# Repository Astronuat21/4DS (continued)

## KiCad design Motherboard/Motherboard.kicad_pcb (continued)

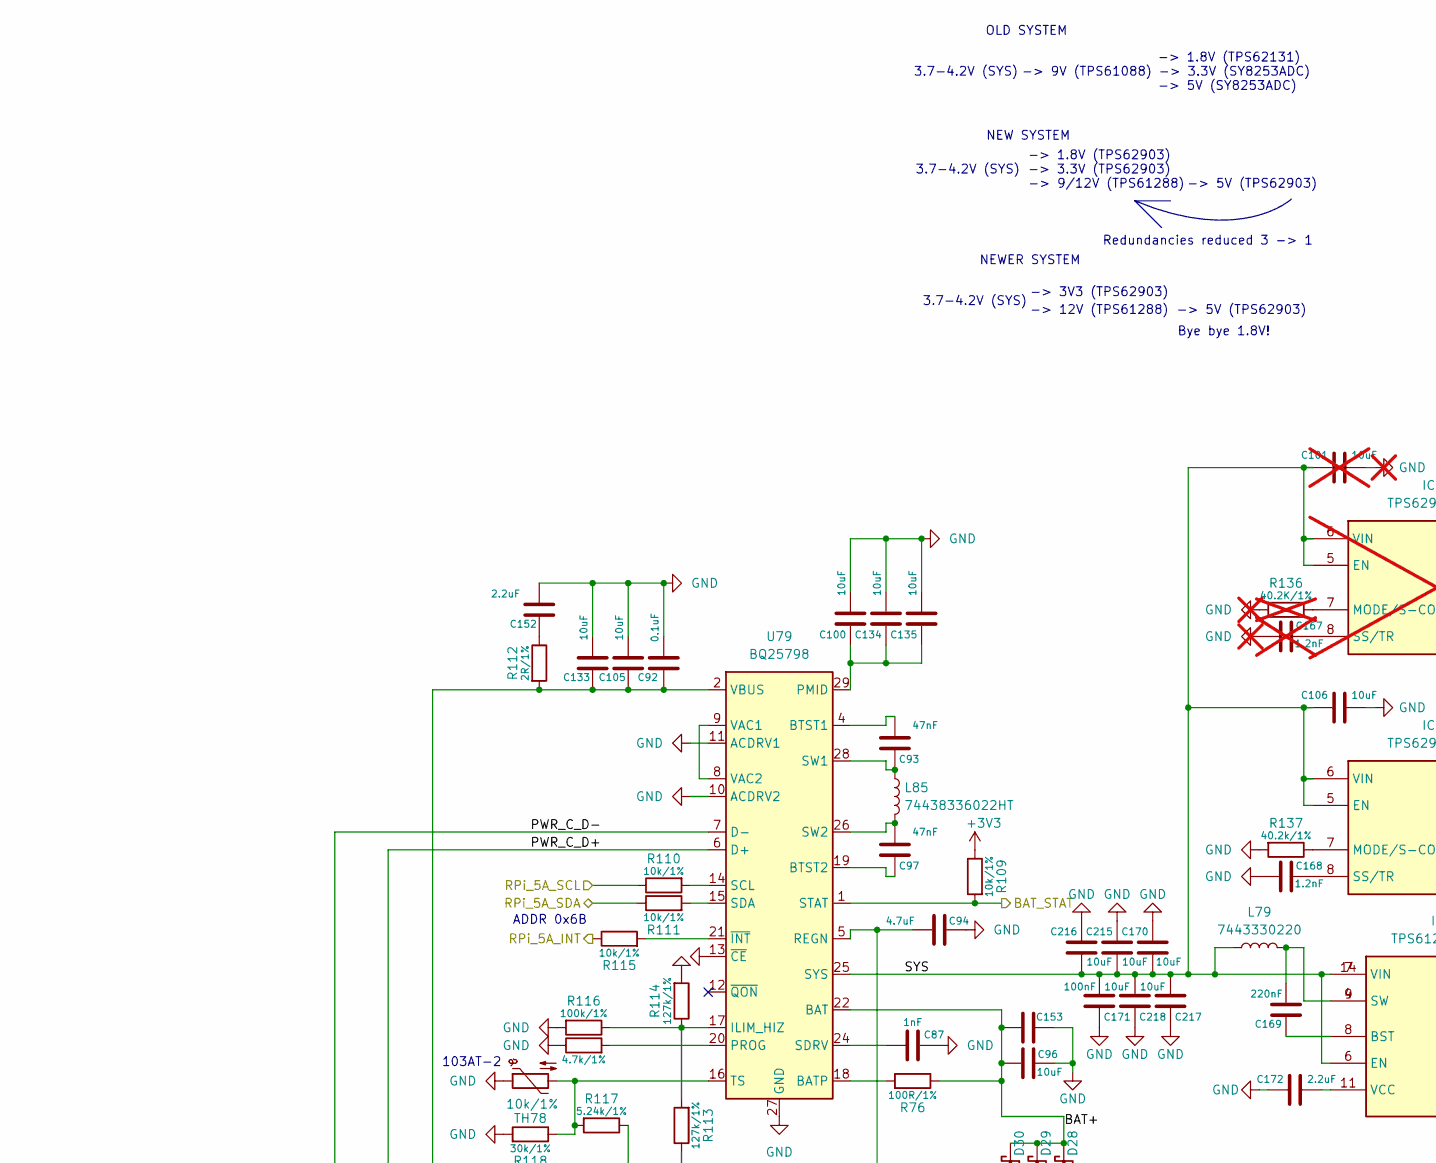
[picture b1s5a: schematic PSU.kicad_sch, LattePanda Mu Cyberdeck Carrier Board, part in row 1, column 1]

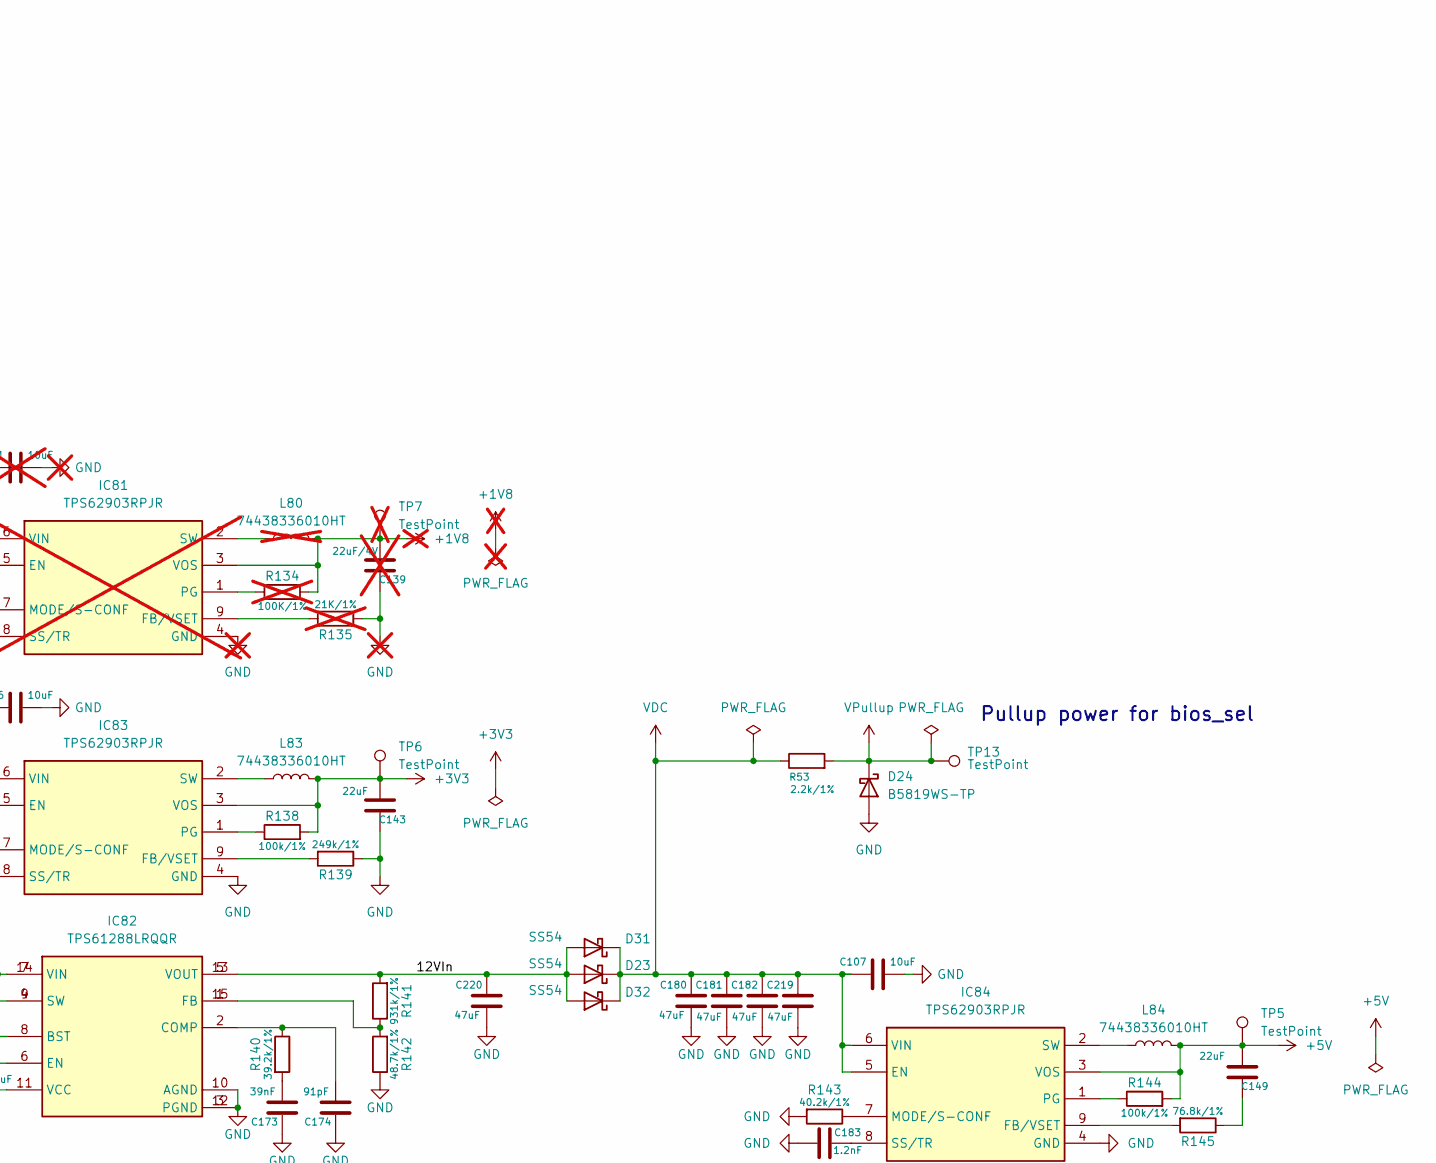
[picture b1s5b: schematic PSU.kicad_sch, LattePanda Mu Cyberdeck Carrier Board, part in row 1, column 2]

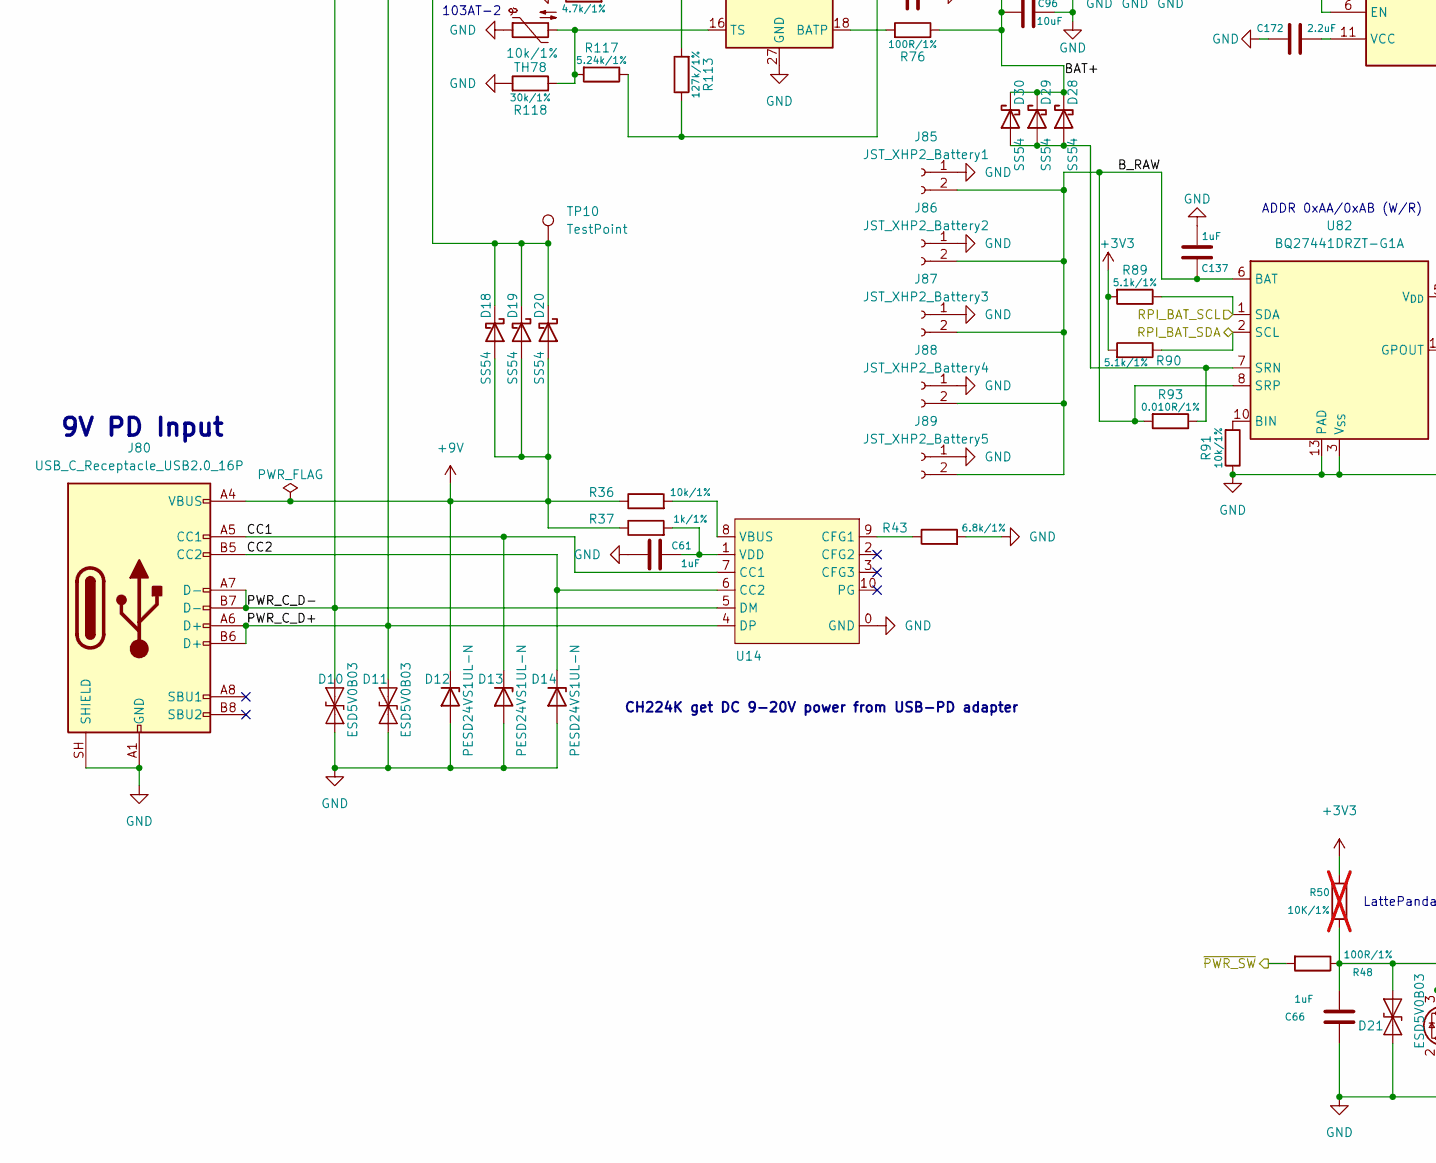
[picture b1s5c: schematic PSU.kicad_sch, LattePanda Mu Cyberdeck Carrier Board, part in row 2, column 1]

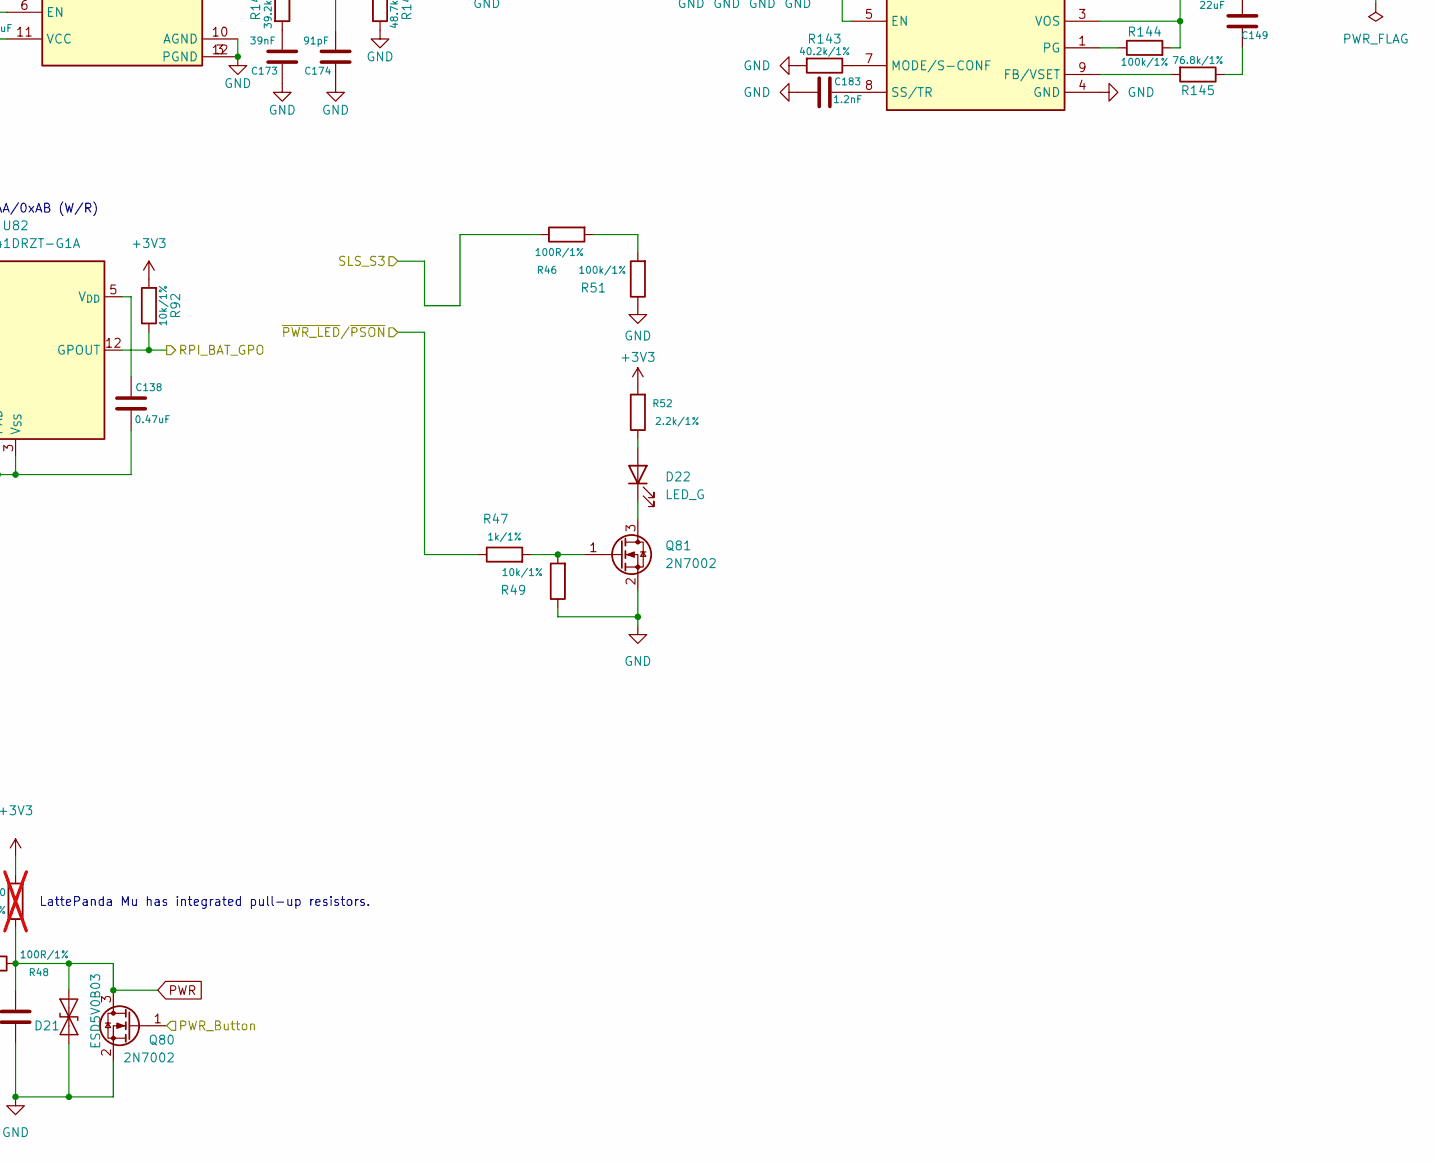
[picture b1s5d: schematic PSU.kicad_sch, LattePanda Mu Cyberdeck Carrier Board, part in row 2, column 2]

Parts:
C61, C66: 1uF; C_0402_1005Metric; MPN TCC0402X5R105M160AT
C87: 1nF; C_0402_1005Metric; MPN CC0402KRX5R9BB102
C92: 0.1uF; C_0402_1005Metric; MPN any/open
C93, C97: 47nF; C_0603_1608Metric; MPN GMK107BJ473KAHT
C94: 4.7uF; C_0402_1005Metric; MPN 0402X475M100NT
C96, C153: 10uF; C_0402_1005Metric; MPN GMC04X5R106M10NT
C100, C105, C133, C134, C135: 10uF; C_0603_1608Metric; MPN CM105X5R106M25AT
C101: 10uF; C_0603_1608Metric; MPN CL10A106MQ8NNWC; not fitted
C106, C170, C215, C216, C217, C218: 10uF; C_0402_1005Metric; MPN GRM155R60J106ME15D
C107: 10uF; C_0805_2012Metric; MPN TCC0805X5R106M160FT
C137: 1uF; C_0402_1005Metric; MPN TCC0402X5R105M100AT
C138: 0.47uF; C_0603_1608Metric; MPN C0603C474K8PACTU
C139: 22uF/4V; C_0805_2012Metric; MPN MCASA21GAB5226MTNA01; not fitted
C143: 22uF; C_0805_2012Metric; MPN MCASA21GAB5226MTNA01
C149: 22uF; C_0805_2012Metric; MPN GRM21BR61A226ME44L
C152, C172: 2.2uF; C_0603_1608Metric; MPN C1608X5R1E225KTJ00N
C167: 1.2nF; C_0402_1005Metric; MPN 0402B122K500CT; not fitted
C168, C183: 1.2nF; C_0402_1005Metric; MPN 0402B122K500CT
C169: 220nF; C_0402_1005Metric; MPN GRM155R61A224KE19D
C171: 100nF; C_0603_1608Metric; MPN C0603C104K9RACTU
C173: 39nF; C_0402_1005Metric; MPN GRM155R61A393KA01D
C174: 91pF; C_0402_1005Metric; MPN GRM1555C1H910JA01D
C180, C181, C182, C219, C220: 47uF; C_1210_3225Metric; MPN C1210C476M4PACTU
D10, D11, D21: ESD5V0B03; D_0402_1005Metric; MPN ESD5V0B03-1006
D12, D13, D14: PESD24VS1UL-N; D_0402_1005Metric; MPN PESD24VS1UL-N
D18, D19, D20, D23, D28, D29, D30, D31, D32: SS54; D_SMA; MPN SS54
D22: LED_G; LED_0603_1608Metric; MPN XL-1608UGC-04
D24: B5819WS-TP; D_SOD-323; MPN B5819WS-TP
IC81: TPS62903RPJR; MPN TPS62903RPJR; not fitted
IC82: TPS61288LRQQR; PTPS61288RQQR; MPN TPS61288LRQQR
IC83, IC84: TPS62903RPJR; MPN TPS62903RPJR
J80: USB_C_Receptacle_USB2.0_16P; USB_C_Receptacle_GCT_USB4105-xx-A_16P_TopMnt_Horizontal; MPN USB4105-GF-A
J85: JST_XHP2_Battery1; JST_XH_B2B-XH-A_1x02_P2.50mm_Vertical; MPN B2B-XH-A
J86: JST_XHP2_Battery2; JST_XH_B2B-XH-A_1x02_P2.50mm_Vertical; MPN B2B-XH-A
J87: JST_XHP2_Battery3; JST_XH_B2B-XH-A_1x02_P2.50mm_Vertical; MPN B2B-XH-A
J88: JST_XHP2_Battery4; JST_XH_B2B-XH-A_1x02_P2.50mm_Vertical; MPN B2B-XH-A
J89: JST_XHP2_Battery5; JST_XH_B2B-XH-A_1x02_P2.50mm_Vertical; MPN B2B-XH-A
L79: 7443330220; WE-HCC_109021; MPN 7443330220
L80: 74438336010HT; MPN 74438336010HT; not fitted
L83, L84: 74438336010HT; MPN 74438336010HT
L85: 74438336022HT; MPN 74438336022HT
Q80, Q81: 2N7002; SOT-23; MPN 2N7002
R36, R49, R92, R109, R110, R111, R115: 10k/1%; R_0402_1005Metric; MPN MCR01MZPF1002
R37, R47: 1k/1%; R_0402_1005Metric; MPN CQ02WGF1001TCE
R43: 6.8k/1%; R_0402_1005Metric; MPN NQ02WGF6801TCE
R46, R48: 100R/1%; R_0402_1005Metric; MPN AC0402FR-07100RL
R50: 10K/1%; R_0402_1005Metric; not fitted
R51, R116, R138, R144: 100k/1%; R_0402_1005Metric; MPN SFR01MZPF1003
R52, R53: 2.2k/1%; R_0402_1005Metric; MPN NQ02WGF2201TCE
R76: 100R/1%; R_1206_3216Metric; MPN NQ06W4F1000T5E
R77: 4.7k/1%; R_0402_1005Metric; MPN CQ02WGF4701TCE
R89, R90: 5.1k/1%; R_0402_1005Metric; MPN AC0402FR-075K1L
R91: 10k/1%; R_0402_1005Metric; MPN KTR03EZPF1002
R93: 0.010R/1%; R_2512_6332Metric; MPN WSLP2512R0100FED
R112: 2R/1%; R_0805_2012Metric; MPN AC0805FR-072RL
R113, R114: 127k/1%; R_0402_1005Metric; MPN 0402WGF1273TCE
R117: 5.24k/1%; R_0402_1005Metric; MPN CR0402-FX-5231GLF
R118: 30k/1%; R_0402_1005Metric; MPN NQ02WGF3002TCE
R134: 100K/1%; R_0402_1005Metric; MPN SFR01MZPF1003; not fitted
R135: 21K/1%; R_0402_1005Metric; MPN RC0402FR-0721KL; not fitted
R136: 40.2K/1%; R_0402_1005Metric; MPN CRCW040240K2FKED; not fitted
R137, R143: 40.2k/1%; R_0402_1005Metric; MPN CRCW040240K2FKED
R139: 249k/1%; R_0402_1005Metric; MPN 0402WGF2493TCE
R140: 39.2k/1%; R_0402_1005Metric; MPN any/open
R141: 931k/1%; R_0402_1005Metric
R142: 48.7k/1%; R_0402_1005Metric; MPN CRCW040248K7FKED
R145: 76.8k/1%; R_0402_1005Metric; MPN NQ02WGF7682TCE
TH78: 10k/1%; R_0603_1608Metric; MPN 103AT-2
TP5, TP6, TP10, TP13: TestPoint; TestPoint_Pad_D1.5mm
TP7: TestPoint; TestPoint_Pad_D1.5mm; not fitted
U14: CH224K; ESSOP-10-1EP_3.9x5mm_P1.0mm_EP3.2x2.3; MPN CH224K
U79: BQ25798; Texas_RQM0029A_VQFN-29_4x4mm_P0.4mm; MPN BQ25798RQMR
U82: BQ27441DRZT-G1A; Texas_S-PDSO-N12; MPN BQ27441DRZT-G1A

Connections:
+3V3: C143.1, IC83.3 (VOS), L83.2, R50.2, R52.2, R89.2, R90.2, R92.2, R109.1, R138.2, TP6.1 (1_1); also elsewhere on the board
+5V: C149.1, IC84.3 (VOS), L84.2, R144.2, TP5.1 (1_1); also elsewhere on the board
+9V: D12.1 (K), D18.2 (A), D19.2 (A), D20.2 (A), J80.A4 (VBUS), J80.A9 (VBUS), J80.B4 (VBUS), J80.B9 (VBUS), R36.1, R37.1
/EXIO/PWR_Button: Q80.1 (G); also elsewhere on the board
/LattePanda Module/RPI_BAT_GPO: R92.1, U82.12 (GPOUT); also elsewhere on the board
/LattePanda Module/RPI_BAT_SCL: R89.1, U82.1 (SDA); also elsewhere on the board
/LattePanda Module/RPI_BAT_SDA: R90.1, U82.2 (SCL); also elsewhere on the board
/LattePanda Module/RPI_BAT_STAT: R109.2, U79.1 (STAT); also elsewhere on the board
/LattePanda Module/RPi_5A_INT: R115.1; also elsewhere on the board
/LattePanda Module/RPi_5A_SCL: R110.1; also elsewhere on the board
/LattePanda Module/RPi_5A_SDA: R111.1; also elsewhere on the board
/LattePanda Module/SLS_S3: R46.1; also elsewhere on the board
/LattePanda Module/~PWR_SW: R48.2; also elsewhere on the board
/PSU/12VIn: C220.2, D23.2 (A), D31.2 (A), D32.2 (A), IC82.5 (VOUT), IC82.13 (VOUT), R141.2
/PSU/BAT+: C96.1, C153.1, D28.1 (K), D29.1 (K), D30.1 (K), R76.1, U79.22 (BAT), U79.23 (BAT)
/PSU/B_RAW: C137.2, J85.2, J86.2, J87.2, J88.2, J89.2, R93.2, U82.6 (BAT), U82.8 (SRP)
/PSU/CC1: D13.1 (K), J80.A5 (CC1), U14.7 (CC1)
/PSU/CC2: D14.1 (K), J80.B5 (CC2), U14.6 (CC2)
/PSU/PWR_C_D+: D11.2 (A2), J80.A6 (D+), J80.B6 (D+), U14.4 (DP), U79.6 (D+)
/PSU/PWR_C_D-: D10.2 (A2), J80.A7 (D-), J80.B7 (D-), U14.5 (DM), U79.7 (D-)
/PSU/SYS: C101.1, C106.1, C170.1, C171.2, C215.1, C216.1, C217.1, C218.1, IC81.5 (EN), IC81.6 (VIN), IC82.6 (EN), IC82.7 (VIN), IC82.14 (VIN), IC83.5 (EN), IC83.6 (VIN), L79.1, U79.25 (SYS)
/~PWR_LED/~PSON: R47.1; also elsewhere on the board
GND: C61.2, C66.2, C87.1, C92.1, C94.2, C96.2, C100.1, C101.2, C105.1, C106.2, C107.2, C133.1, C134.1, C135.1, C137.1, C138.1, C139.2, C143.2, C152.1, C153.2, C167.1, C168.1, C170.2, C171.1, C172.2, C173.1, C174.1, C180.1, C181.1, C182.1, C183.1, C215.2, C216.2, C217.2, C218.2, C219.1, C220.1, D10.1 (A1), D11.1 (A1), D12.2 (A), D13.2 (A), D14.2 (A), D21.1 (A1), D24.2 (A), IC81.4 (GND), IC82.3 (PGND), IC82.10 (AGND), IC82.12 (PGND), IC83.4 (GND), IC84.4 (GND), J80.A1 (GND), J80.A12 (GND), J80.B1 (GND), J80.B12 (GND), J80.SH (SHIELD), J85.1, J86.1, J87.1, J88.1, J89.1, Q80.2 (S), Q81.2 (S), R43.2, R49.1, R51.1, R77.1, R91.1, R114.2, R116.2, R118.2, R135.1, R136.2, R137.2, R139.1, R142.1, R143.2, TH78.1, U14.0 (GND), U79.10 (ACDRV2), U79.11 (ACDRV1), U79.13 (~CE), U79.27 (GND), U82.3 (V_{SS}), U82.13 (PAD); also elsewhere on the board
unnamed: C139.1, IC81.3 (VOS), L80.2, R134.2, TP7.1
unnamed: C149.2, R145.1
unnamed: C152.2, R112.1
unnamed: C167.2, IC81.8 (SS/TR)
unnamed: C169.2, IC82.4 (SW), IC82.9 (SW), L79.2
unnamed: C173.2, R140.2
unnamed: C92.2, C105.2, C133.2, D18.1 (K), D19.1 (K), D20.1 (K), R112.2, TP10.1 (1_1), U79.2 (VBUS), U79.3 (VBUS)
unnamed: D22.2 (A), R52.1
unnamed: D22.1 (K), Q81.3 (D)
unnamed: D28.2 (A), D29.2 (A), D30.2 (A), R93.1, U82.7 (SRN)
unnamed: IC81.1 (PG), R134.1
unnamed: IC81.2 (SW), L80.1
unnamed: IC81.7 (MODE/S-CONF), R136.1
unnamed: IC81.9 (FB/VSET), R135.2
unnamed: C169.1, IC82.8 (BST)
unnamed: C174.2, IC82.2 (COMP), R140.1
unnamed: IC82.1 (FB), IC82.15 (FB), R141.1, R142.2
unnamed: C172.1, IC82.11 (VCC)
unnamed: IC83.9 (FB/VSET), R139.2
unnamed: IC83.7 (MODE/S-CONF), R137.1
unnamed: IC83.1 (PG), R138.1
unnamed: C168.2, IC83.8 (SS/TR)
unnamed: IC83.2 (SW), L83.1
unnamed: IC84.9 (FB/VSET), R145.2
unnamed: IC84.7 (MODE/S-CONF), R143.1
unnamed: IC84.1 (PG), R144.1
unnamed: C183.2, IC84.8 (SS/TR)
unnamed: IC84.2 (SW), L84.1
unnamed: Q81.1 (G), R47.2, R49.2
unnamed: R46.2, R51.2
unnamed: R43.1, U14.9 (CFG1)
unnamed: R36.2, U14.8 (VBUS)
unnamed: C61.1, R37.2, U14.1 (VDD)
unnamed: R76.2, U79.18 (BATP)
unnamed: C93.1, U79.4 (BTST1)
unnamed: C97.2, U79.19 (BTST2)
unnamed: R113.2, R114.1, R116.1, U79.17 (ILIM_HIZ)
unnamed: C100.2, C134.2, C135.2, U79.29 (PMID)
unnamed: R77.2, U79.20 (PROG)
unnamed: C94.1, R113.1, R117.1, U79.5 (REGN)
unnamed: R110.2, U79.14 (SCL)
unnamed: R111.2, U79.15 (SDA)
unnamed: C87.2, U79.24 (SDRV)
unnamed: C93.2, L85.1, U79.28 (SW1)
unnamed: C97.1, L85.2, U79.26 (SW2)
unnamed: R117.2, R118.1, TH78.2, U79.16 (TS)
unnamed: U79.8 (VAC2), U79.9 (VAC1)
unnamed: R115.2, U79.21 (~INT)
unnamed: R91.2, U82.10 (BIN)
unnamed: C138.2, U82.5 (V_{DD})
PWR: C66.1, D21.2 (A2), Q80.3 (D), R48.1, R50.1
VDC: C107.1, C180.2, C181.2, C182.2, C219.2, D23.1 (K), D31.1 (K), D32.1 (K), IC84.5 (EN), IC84.6 (VIN), R53.1; also elsewhere on the board
VPullup: D24.1 (K), R53.2, TP13.1 (1_1); also elsewhere on the board

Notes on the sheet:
-> 1.8V (TPS62903)
ADDR 0x6B
-> 3V3 (TPS62903)
103AT-2
-> 3.3V (TPS62903)
9V PD Input
NEWER SYSTEM
-> 9/12V (TPS61288)
3.7-4.2V (SYS)
NEW SYSTEM
-> 5V (SY8253ADC)
-> 9V (TPS61088)
LattePanda Mu has integrated pull-up resistors.
OLD SYSTEM
ADDR 0xAA/0xAB (W/R)
-> 1.8V (TPS62131)
Redundancies reduced 3 -> 1
CH224K get DC 9-20V power from USB-PD adapter
-> 5V (TPS62903)
Pullup power for bios_sel
Bye bye 1.8V!
-> 3.3V (SY8253ADC)
-> 12V (TPS61288)

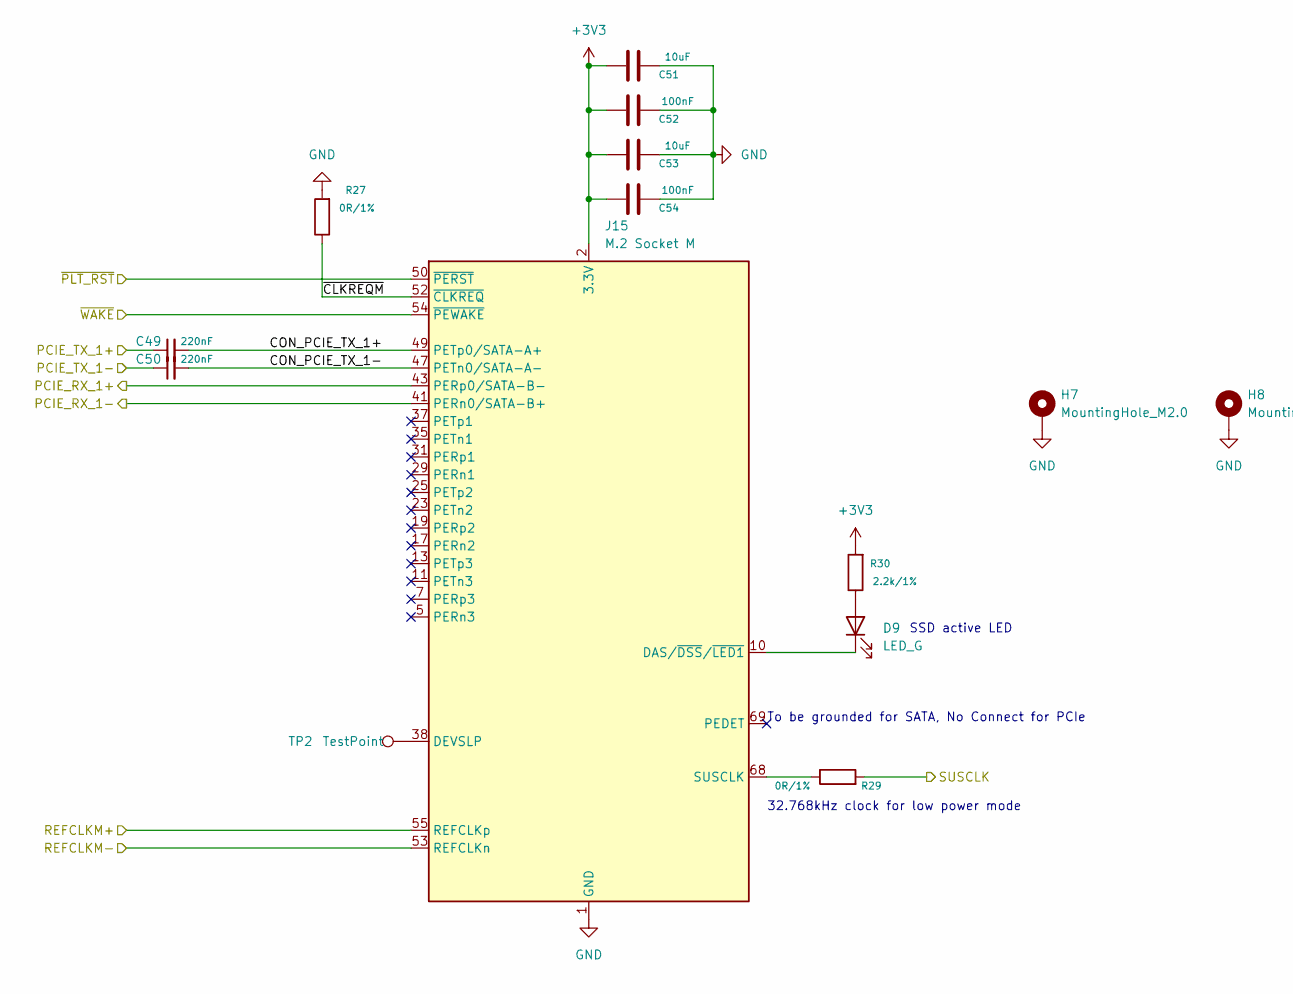
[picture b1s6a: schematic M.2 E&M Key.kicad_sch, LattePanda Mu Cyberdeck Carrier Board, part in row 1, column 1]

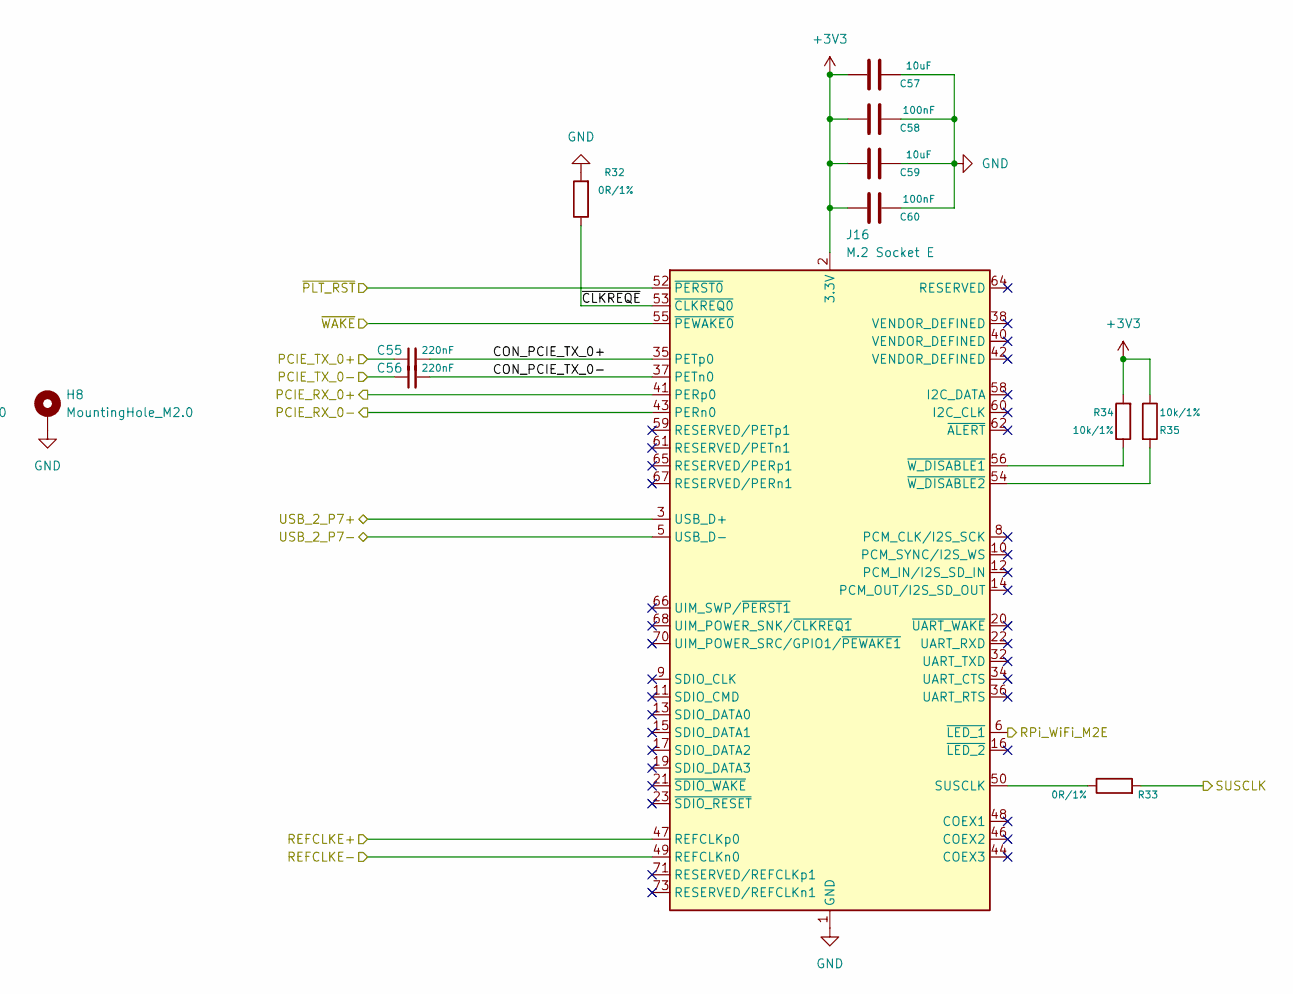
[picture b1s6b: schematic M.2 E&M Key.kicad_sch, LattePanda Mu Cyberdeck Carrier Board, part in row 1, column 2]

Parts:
C49, C50, C55, C56: 220nF; C_0402_1005Metric; MPN GRM155R61H224ME01D
C51, C53, C57, C59: 10uF; C_0402_1005Metric; MPN GMC04X5R106M10NT
C52, C54, C58, C60: 100nF; C_0402_1005Metric; MPN TCC0402X5R104M500AT
D9: LED_G; LED_0603_1608Metric; MPN XL-1608UGC-04
H7, H8: MountingHole_M2.0; MountingHole_3mm_M2_Pad_TopOnly; MPN SMTWEM225STR
J15: M.2 Socket M; MDT420M03001; MPN APCI0107-P001A
J16: M.2 Socket E; MDT420E03001; MPN APCI0108-P001A
R27, R29, R32, R33: 0R/1%; R_0402_1005Metric; MPN CQ02WGF0000TCE
R30: 2.2k/1%; R_0402_1005Metric; MPN NQ02WGF2201TCE
R34, R35: 10k/1%; R_0402_1005Metric; MPN MCR01MZPF1002
TP2: TestPoint; TestPoint_Pad_D1.5mm

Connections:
+3V3: C51.2, C52.2, C53.2, C54.2, C57.2, C58.2, C59.2, C60.2, J15.2 (3.3V), J15.4 (3.3V), J15.12 (3.3V), J15.14 (3.3V), J15.16 (3.3V), J15.18 (3.3V), J15.70 (3.3V), J15.72 (3.3V), J15.74 (3.3V), J16.2 (3.3V), J16.4 (3.3V), J16.72 (3.3V), J16.74 (3.3V), R30.2, R34.2, R35.1; also elsewhere on the board
/LattePanda Module/HSIO_2_RX+: J15.43 (PERp0/SATA-B-); also elsewhere on the board
/LattePanda Module/HSIO_2_RX-: J15.41 (PERn0/SATA-B+); also elsewhere on the board
/LattePanda Module/HSIO_2_TX+: C49.1; also elsewhere on the board
/LattePanda Module/HSIO_2_TX-: C50.1; also elsewhere on the board
/LattePanda Module/HSIO_3_RX+: J16.41 (PERp0); also elsewhere on the board
/LattePanda Module/HSIO_3_RX-: J16.43 (PERn0); also elsewhere on the board
/LattePanda Module/HSIO_3_TX+: C55.1; also elsewhere on the board
/LattePanda Module/HSIO_3_TX-: C56.1; also elsewhere on the board
/LattePanda Module/REFCLK0+: J15.53 (REFCLKn); also elsewhere on the board
/LattePanda Module/REFCLK0-: J15.55 (REFCLKp); also elsewhere on the board
/LattePanda Module/REFCLK3+: J16.47 (REFCLKp0); also elsewhere on the board
/LattePanda Module/REFCLK3-: J16.49 (REFCLKn0); also elsewhere on the board
/LattePanda Module/SUSCLK_WIFI: R29.2, R33.2; also elsewhere on the board
/LattePanda Module/USB_2_P7+: J16.3 (USB_D+); also elsewhere on the board
/LattePanda Module/USB_2_P7-: J16.5 (USB_D-); also elsewhere on the board
/LattePanda Module/WiFi_M2E_LED: J16.6 (~LED_1); also elsewhere on the board
/M.2 E&M Key/CON_PCIE_TX_0+: C55.2, J16.35 (PETp0)
/M.2 E&M Key/CON_PCIE_TX_0-: C56.2, J16.37 (PETn0)
/M.2 E&M Key/CON_PCIE_TX_1+: C49.2, J15.49 (PETp0/SATA-A+)
/M.2 E&M Key/CON_PCIE_TX_1-: C50.2, J15.47 (PETn0/SATA-A-)
/M.2 E&M Key/~CLKREQE: J16.53 (~CLKREQ0), R32.1
/M.2 E&M Key/~CLKREQM: J15.52 (~CLKREQ), R27.1
/~PLT_RST: J15.50 (~PERST), J16.52 (~PERST0); also elsewhere on the board
/~WAKE: J15.54 (~PEWAKE), J16.55 (~PEWAKE0); also elsewhere on the board
GND: C51.1, C52.1, C53.1, C54.1, C57.1, C58.1, C59.1, C60.1, H7.1 (1_1), H8.1 (1_1), J15.1 (GND), J15.3 (GND), J15.9 (GND), J15.15 (GND), J15.21 (GND), J15.27 (GND), J15.33 (GND), J15.39 (GND), J15.45 (GND), J15.51 (GND), J15.57 (GND), J15.71 (GND), J15.73 (GND), J15.75 (GND), J15.MP1, J15.MP2, J16.1 (GND), J16.7 (GND), J16.18 (GND), J16.33 (GND), J16.39 (GND), J16.45 (GND), J16.51 (GND), J16.57 (GND), J16.63 (GND), J16.69 (GND), J16.75 (GND), J16.MP1, J16.MP2, R27.2, R32.2; also elsewhere on the board
unnamed: D9.2 (A), R30.1
unnamed: D9.1 (K), J15.10 (DAS/~DSS/~LED1)
unnamed: J15.38 (DEVSLP), TP2.1 (1_1)
unnamed: J15.68 (SUSCLK), R29.1
unnamed: J16.50 (SUSCLK), R33.1
unnamed: J16.56 (~W_DISABLE1), R34.1
unnamed: J16.54 (~W_DISABLE2), R35.2

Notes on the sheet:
To be grounded for SATA, No Connect for PCIe
SSD active LED
32.768kHz clock for low power mode

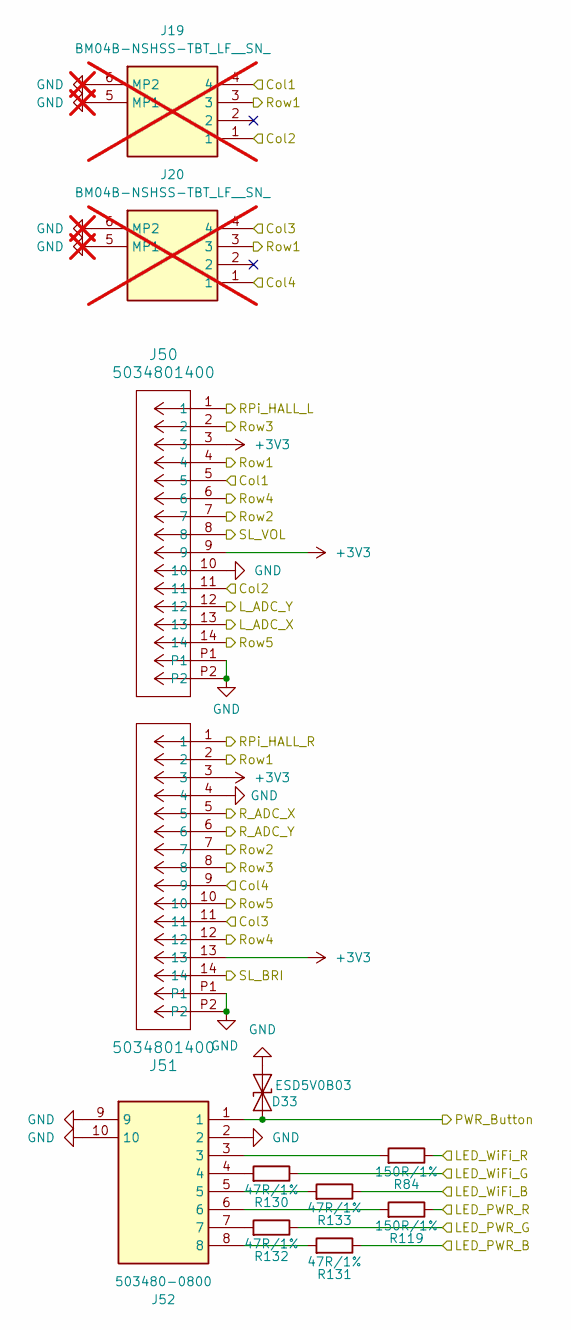
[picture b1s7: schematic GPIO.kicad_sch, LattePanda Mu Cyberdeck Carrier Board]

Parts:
D33: ESD5V0B03; D_0402_1005Metric; MPN ESD5V0B03-1006
J19, J20: BM04B-NSHSS-TBT_LF__SN_; BM04BNSHSSTBTLFSN; not fitted
J50, J51: 5034801400; MPN 5034801400
J52: 503480-0800; 5034800800; MPN 5034800800
R84, R119: 150R/1%; R_0402_1005Metric; MPN 0402WGF1500TCE
R130, R131, R132, R133: 47R/1%; R_0402_1005Metric; MPN AC0402FR-0747RL

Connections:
+3V3: J50.3, J50.9, J51.3, J51.13; also elsewhere on the board
/EXIO/Col1: J19.4, J50.5; also elsewhere on the board
/EXIO/Col2: J19.1, J50.11; also elsewhere on the board
/EXIO/Col3: J20.4, J51.11; also elsewhere on the board
/EXIO/Col4: J20.1, J51.9; also elsewhere on the board
/EXIO/LED_PWR_B: R131.1; also elsewhere on the board
/EXIO/LED_PWR_G: R132.1; also elsewhere on the board
/EXIO/LED_PWR_R: R119.1; also elsewhere on the board
/EXIO/LED_WiFi_B: R133.1; also elsewhere on the board
/EXIO/LED_WiFi_G: R130.1; also elsewhere on the board
/EXIO/LED_WiFi_R: R84.1; also elsewhere on the board
/EXIO/L_ADC_X: J50.13; also elsewhere on the board
/EXIO/L_ADC_Y: J50.12; also elsewhere on the board
/EXIO/PWR_Button: D33.1 (A1), J52.1; also elsewhere on the board
/EXIO/RPi_HALL_L: J50.1; also elsewhere on the board
/EXIO/RPi_HALL_R: J51.1; also elsewhere on the board
/EXIO/R_ADC_X: J51.5; also elsewhere on the board
/EXIO/R_ADC_Y: J51.6; also elsewhere on the board
/EXIO/Row1: J19.3, J20.3, J50.4, J51.2; also elsewhere on the board
/EXIO/Row2: J50.7, J51.7; also elsewhere on the board
/EXIO/Row3: J50.2, J51.8; also elsewhere on the board
/EXIO/Row4: J50.6, J51.12; also elsewhere on the board
/EXIO/Row5: J50.14, J51.10; also elsewhere on the board
/EXIO/SL_BRI: J51.14; also elsewhere on the board
/EXIO/SL_VOL: J50.8; also elsewhere on the board
GND: D33.2 (A2), J19.5 (MP1), J19.6 (MP2), J20.5 (MP1), J20.6 (MP2), J50.10, J50.P1, J50.P2, J51.4, J51.P1, J51.P2, J52.2, J52.9, J52.10; also elsewhere on the board
unnamed: J52.3, R84.2
unnamed: J52.4, R130.2
unnamed: J52.5, R133.2
unnamed: J52.6, R119.2
unnamed: J52.7, R132.2
unnamed: J52.8, R131.2

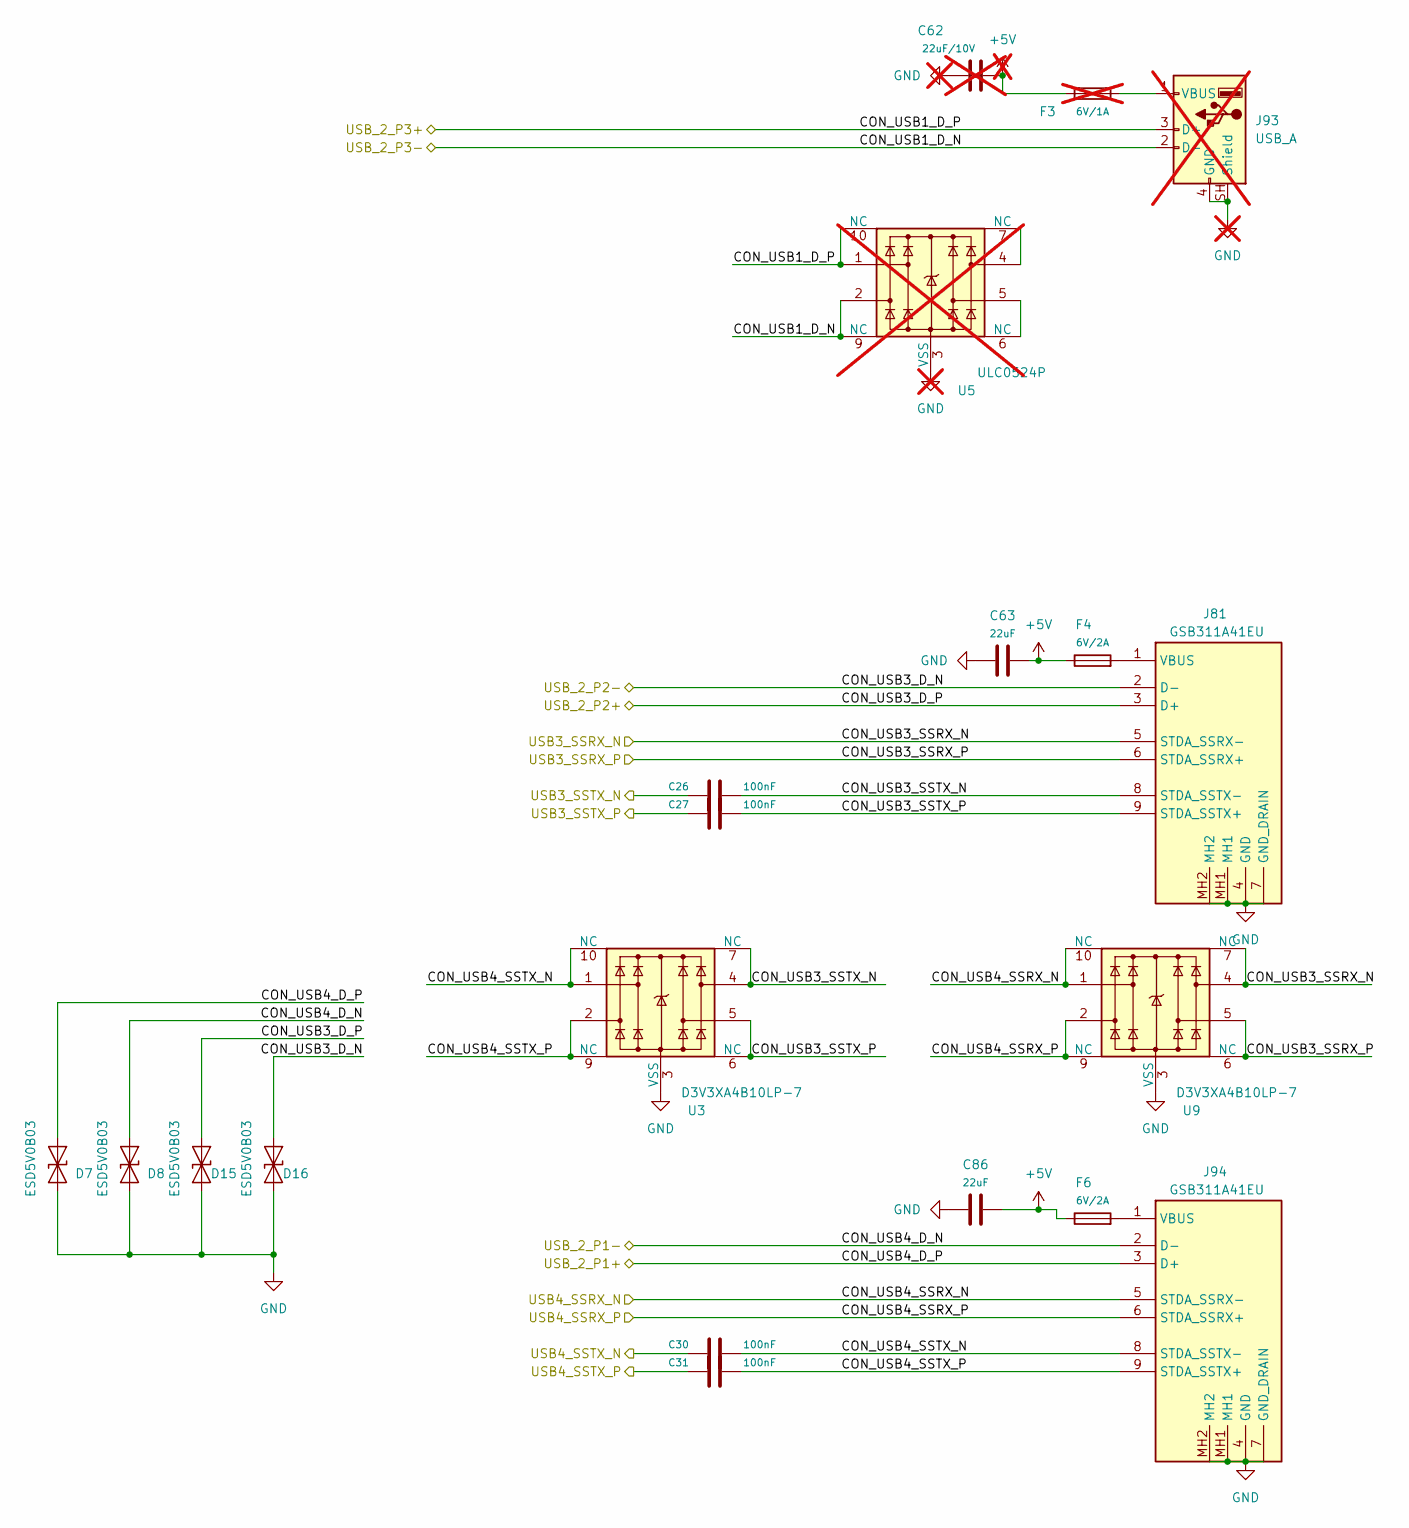
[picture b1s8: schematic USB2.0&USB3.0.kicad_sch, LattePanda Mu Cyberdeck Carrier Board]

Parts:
C26, C27, C30, C31: 100nF; C_0402_1005Metric; MPN TCC0402X5R104M500AT
C62: 22uF/10V; C_0603_1608Metric; not fitted
C63, C86: 22uF; C_0603_1608Metric; MPN CL10A226MP8NUNE
D7, D8, D15, D16: ESD5V0B03; D_0402_1005Metric; MPN ESD5V0B03-1006
F3: 6V/1A; Fuse_0805_2012Metric; not fitted
F4, F6: 6V/2A; Fuse_0805_2012Metric; MPN SMD0805B110TF
J81, J94: GSB311A41EU; MPN GSB311A41EU
J93: USB_A; USB_A_Molex_48037-2200_Horizontal; not fitted
U3, U9: D3V3XA4B10LP-7; Diodes_UDFN-10_1x2.5mm_P0.5mm; MPN D3V3XA4B10LP-7
U5: ULC0524P; Diodes_UDFN-10_1.0x2.5mm_P0.5mm; not fitted

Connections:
+5V: C62.2, C63.2, C86.2, F3.1, F4.1, F6.1; also elsewhere on the board
/LattePanda Module/HSIO_0_TX+: C27.1; also elsewhere on the board
/LattePanda Module/HSIO_0_TX-: C26.1; also elsewhere on the board
/LattePanda Module/HSIO_1_TX+: C31.1; also elsewhere on the board
/LattePanda Module/HSIO_1_TX-: C30.1; also elsewhere on the board
/USB/CON_USB3_D_N: D16.2 (A2), J81.2 (D-); also elsewhere on the board
/USB/CON_USB3_D_P: D15.2 (A2), J81.3 (D+); also elsewhere on the board
/USB/CON_USB3_SSRX_N: J81.5 (STDA_SSRX-), U9.4, U9.7 (NC); also elsewhere on the board
/USB/CON_USB3_SSRX_P: J81.6 (STDA_SSRX+), U9.5, U9.6 (NC); also elsewhere on the board
/USB/CON_USB3_SSTX_N: C26.2, J81.8 (STDA_SSTX-), U3.4, U3.7 (NC)
/USB/CON_USB3_SSTX_P: C27.2, J81.9 (STDA_SSTX+), U3.5, U3.6 (NC)
/USB/CON_USB4_D_N: D8.2 (A2), J94.2 (D-); also elsewhere on the board
/USB/CON_USB4_D_P: D7.2 (A2), J94.3 (D+); also elsewhere on the board
/USB/CON_USB4_SSRX_N: J94.5 (STDA_SSRX-), U9.1, U9.10 (NC); also elsewhere on the board
/USB/CON_USB4_SSRX_P: J94.6 (STDA_SSRX+), U9.2, U9.9 (NC); also elsewhere on the board
/USB/CON_USB4_SSTX_N: C30.2, J94.8 (STDA_SSTX-), U3.1, U3.10 (NC)
/USB/CON_USB4_SSTX_P: C31.2, J94.9 (STDA_SSTX+), U3.2, U3.9 (NC)
GND: C62.1, C63.1, C86.1, D7.1 (A1), D8.1 (A1), D15.1 (A1), D16.1 (A1), J81.4 (GND), J81.7 (GND_DRAIN), J81.MH1, J81.MH2, J93.4 (GND), J93.SH (Shield), J94.4 (GND), J94.7 (GND_DRAIN), J94.MH1, J94.MH2, U3.3 (VSS), U3.8 (VSS), U5.3 (VSS), U5.8 (VSS), U9.3 (VSS), U9.8 (VSS); also elsewhere on the board
unnamed: F3.2, J93.1 (VBUS)
unnamed: F4.2, J81.1 (VBUS)
unnamed: J93.2 (D-), U5.2, U5.9 (NC)
unnamed: J93.3 (D+), U5.1, U5.10 (NC)
unnamed: F6.2, J94.1 (VBUS)
unnamed: U5.4, U5.7 (NC)
unnamed: U5.5, U5.6 (NC)

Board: 4 copper layers, 364 parts (2 on the bottom side), 327 nets, no tracks yet.

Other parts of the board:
M1#2: Fan_4pin; JST_PH_B4B-PH-K_1x04_P2.00mm_Vertical

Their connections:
GND: M1#2.1 (-); also elsewhere on the board
unnamed 251: M1#2.3 (Tacho); also elsewhere on the board
unnamed 297: M1#2.4 (PWM); also elsewhere on the board
